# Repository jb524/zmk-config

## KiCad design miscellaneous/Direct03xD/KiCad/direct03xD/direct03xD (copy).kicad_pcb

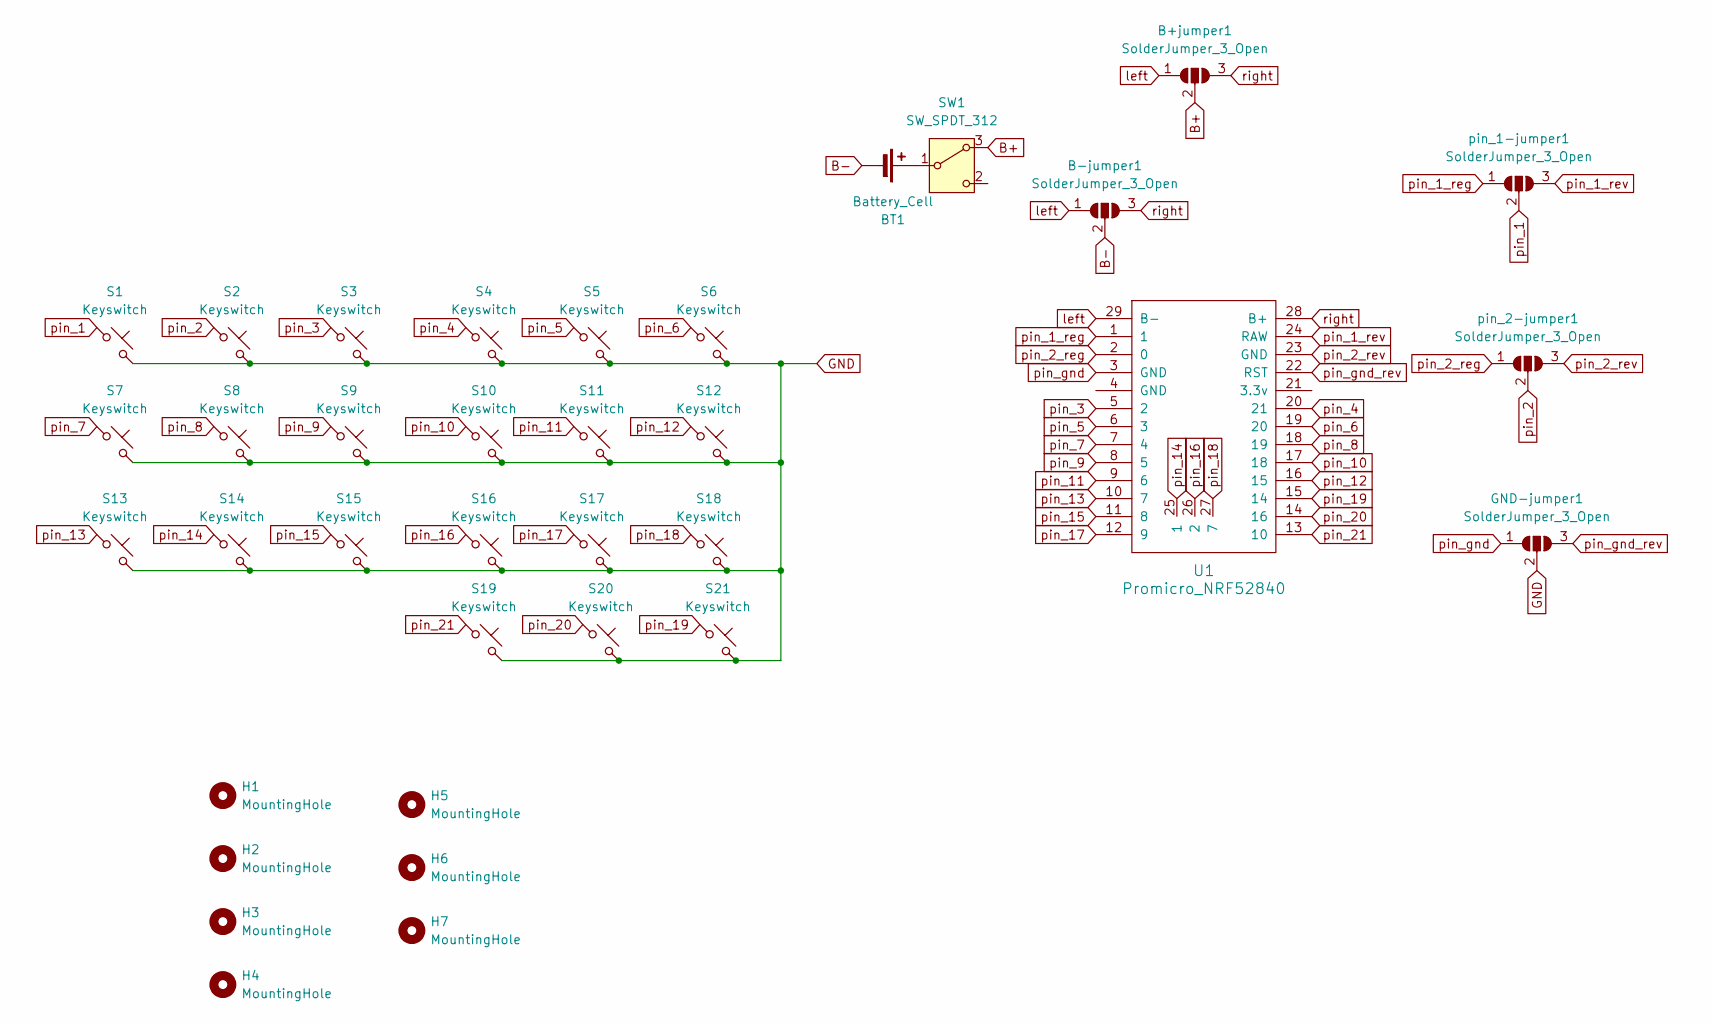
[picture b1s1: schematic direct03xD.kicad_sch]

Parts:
B+jumper1: SolderJumper_3_Open; jumper
B-jumper1: SolderJumper_3_Open; jumper
BT1: Battery_Cell; Battery pins
GND-jumper1: SolderJumper_3_Open; jumper
H1, H2, H3, H4, H5, H6, H7: MountingHole; MountingHole_2.2mm_M2
S1, S2, S3, S4, S5, S6, S7, S8, S9, S10, S11, S12, S13, S14, S15, S16, S17, S18, S19, S20, S21: Keyswitch; MX_1.00u_reversible_solderswap_18.5mm
SW1: SW_SPDT_312; powerswitch_SK12D07VG
U1: Promicro_NRF52840; Promicro_nrf52840_unprinted
pin_1-jumper1, pin_2-jumper1: SolderJumper_3_Open; jumper

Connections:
B+: B+jumper1.2 (C), SW1.3 (A)
B-: B-jumper1.2 (C), BT1.2 (-)
GND: GND-jumper1.2 (C), S1.2, S2.2, S3.2, S4.2, S5.2, S6.2, S7.2, S8.2, S9.2, S10.2, S11.2, S12.2, S13.2, S14.2, S15.2, S16.2, S17.2, S18.2, S19.2, S20.2, S21.2
unnamed: BT1.1 (+), SW1.1 (B)
left: B+jumper1.1 (A), B-jumper1.1 (A), U1.29 (B-)
pin_1: S1.1, pin_1-jumper1.2 (C)
pin_1_reg: U1.1, pin_1-jumper1.1 (A)
pin_1_rev: U1.24 (RAW), pin_1-jumper1.3 (B)
pin_2: S2.1, pin_2-jumper1.2 (C)
pin_2_reg: U1.2 (0), pin_2-jumper1.1 (A)
pin_2_rev: U1.23 (GND), pin_2-jumper1.3 (B)
pin_3: S3.1, U1.5 (2)
pin_4: S4.1, U1.20 (21)
pin_5: S5.1, U1.6 (3)
pin_6: S6.1, U1.19 (20)
pin_7: S7.1, U1.7 (4)
pin_8: S8.1, U1.18 (19)
pin_9: S9.1, U1.8 (5)
pin_10: S10.1, U1.17 (18)
pin_11: S11.1, U1.9 (6)
pin_12: S12.1, U1.16 (15)
pin_13: S13.1, U1.10 (7)
pin_14: S14.1, U1.25 (1)
pin_15: S15.1, U1.11 (8)
pin_16: S16.1, U1.26 (2)
pin_17: S17.1, U1.12 (9)
pin_18: S18.1, U1.27 (7)
pin_19: S21.1, U1.15 (14)
pin_20: S20.1, U1.14 (16)
pin_21: S19.1, U1.13 (10)
pin_gnd: GND-jumper1.1 (A), U1.3 (GND)
pin_gnd_rev: GND-jumper1.3 (B), U1.22 (RST)
right: B+jumper1.3 (B), B-jumper1.3 (B), U1.28 (B+)

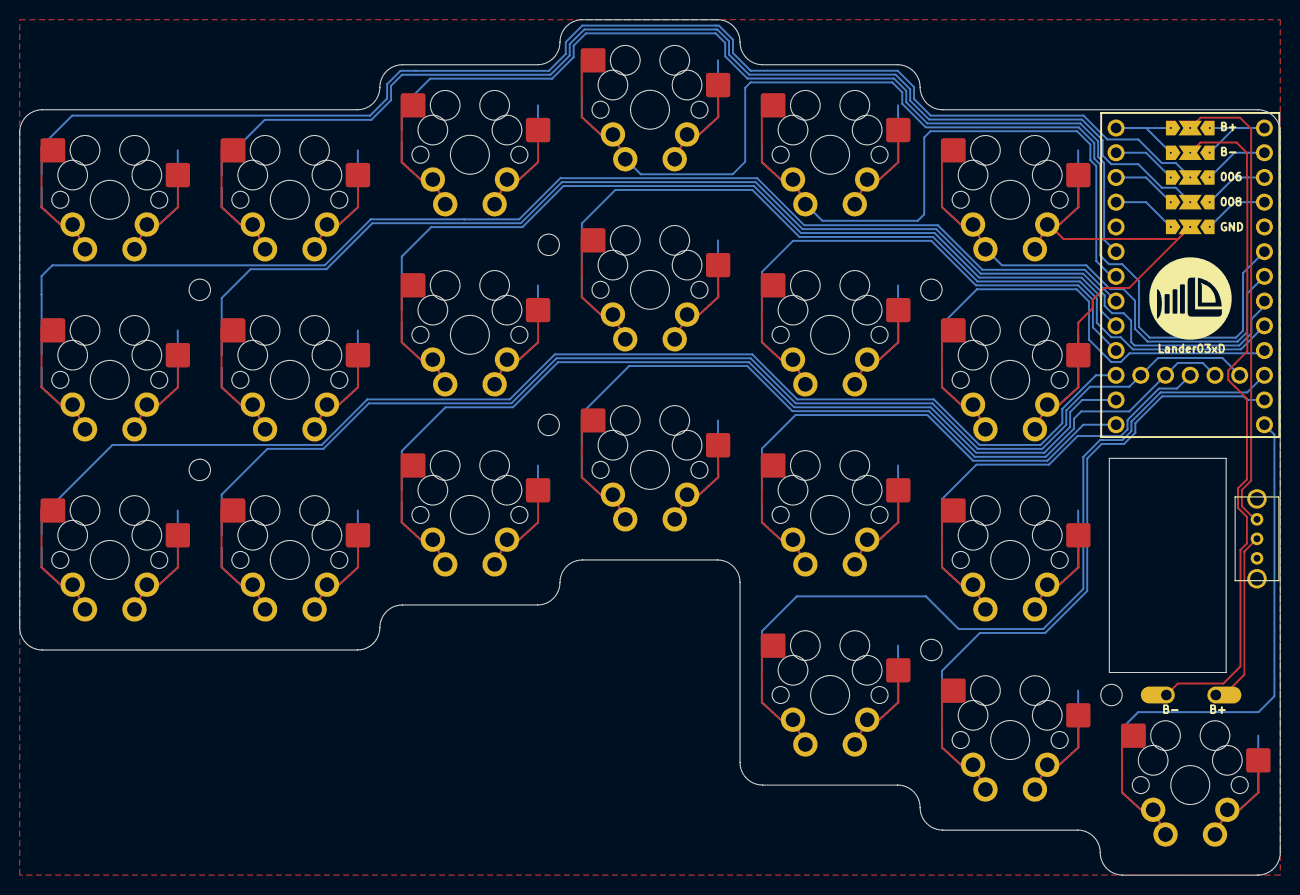
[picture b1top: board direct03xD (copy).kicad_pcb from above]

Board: 2 copper layers, 129.5 x 87.9 mm, 36 parts (0 on the bottom side), 33 nets.

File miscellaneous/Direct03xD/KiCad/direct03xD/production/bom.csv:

Designator,Footprint,Quantity,Value,LCSC Part #
BT1,Battery pins,1,Battery_Cell,
"S1, S10, S11, S12, S13, S14, S15, S16, S17, S18, S19, S2, S20, S21, S3, S4, S5, S6, S7, S8, S9",MX_1.00u_reversible_solderswap_18.5mm,21,Keyswitch,
SW1,powerswitch_SK12D07VG,1,SW_SPDT_312,
U1,Promicro_nrf52840_unprinted,1,Promicro_NRF52840,

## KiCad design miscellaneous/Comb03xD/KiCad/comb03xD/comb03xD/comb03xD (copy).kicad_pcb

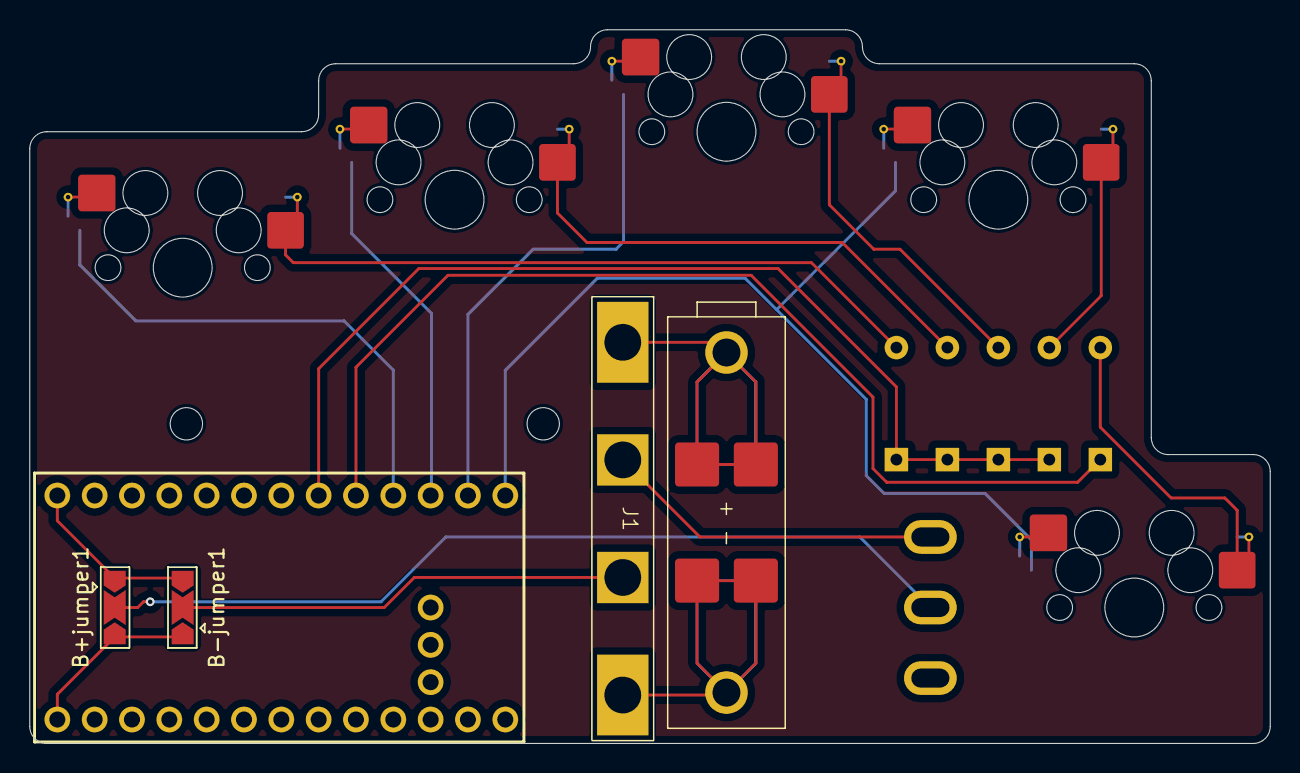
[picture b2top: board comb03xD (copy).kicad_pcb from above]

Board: 2 copper layers, 84.4 x 48.6 mm, 18 parts (0 on the bottom side), 18 nets.

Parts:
B+jumper1: SolderJumper_3_Open; SolderJumper-3_P2.0mm_Open_TrianglePad1.0x1.5mm
B-jumper1: SolderJumper_3_Open; SolderJumper-3_P2.0mm_Open_TrianglePad1.0x1.5mm
BT1: Battery_Cell; SbM-9202_14250_battery_holder
D1, D2, D3, D4, D5: Diode; Diode_DO-35_DO35_unprinted
H1, H2: MountingHole; MountingHole_2.2mm_M2
J1: Conn_01x04_Socket; BMS 1S
S1, S2, S3, S4, S5: Keyswitch; Hotswap_MX_1.00u_reversible_18.5mm
SW1: SW_SPDT_312; SW_Vertical_Slide_5mm
U1: Promicro_NRF52840; Promicro_nrf52840

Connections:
B+: BT1.1 (+), J1.1
B-: BT1.2 (-), J1.4
unnamed: D1.2 (A), S1.2
unnamed: D2.2 (A), S2.2
unnamed: D3.2 (A), S3.2
unnamed: D4.2 (A), S4.2
unnamed: D5.2 (A), S5.2
P+: B+jumper1.2 (C), SW1.1 (B)
P-: B-jumper1.2 (C), J1.3
Ps+: J1.2, SW1.3 (A)
col_1: S1.1, U1.16 (15)
col_2: S2.1, U1.15 (14)
col_3: S3.1, U1.14 (16)
col_4: S4.1, S5.1, U1.13 (10)
left: B+jumper1.3 (B), B-jumper1.1 (A), U1.29 (B-)
right: B+jumper1.1 (A), B-jumper1.3 (B), U1.28 (B+)
row_1: D1.1 (K), D2.1 (K), D3.1 (K), D4.1 (K), U1.18 (19)
row_2: D5.1 (K), U1.17 (18)

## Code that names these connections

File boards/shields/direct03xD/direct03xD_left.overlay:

#include "direct03xD.dtsi" // The shared dtsi file is included in the overlay

// Label of the kscan node in the dtsi
&default_kscan {
	input-gpios =  <&gpio0 6 (GPIO_ACTIVE_LOW | GPIO_PULL_UP)>, //Pin_1
			    <&gpio0 8 (GPIO_ACTIVE_LOW | GPIO_PULL_UP)>,//Pin_2
			    <&gpio0 17 (GPIO_ACTIVE_LOW | GPIO_PULL_UP)>,//Pin_3
			    <&gpio0 31 (GPIO_ACTIVE_LOW | GPIO_PULL_UP)>,//Pin_4
			    <&gpio0 20 (GPIO_ACTIVE_LOW | GPIO_PULL_UP)>,//Pin_5
			    <&gpio0 29 (GPIO_ACTIVE_LOW | GPIO_PULL_UP)>,//Pin_6
			    <&gpio0 22 (GPIO_ACTIVE_LOW | GPIO_PULL_UP)>,//Pin_7
			    <&gpio0 2 (GPIO_ACTIVE_LOW | GPIO_PULL_UP)>,//Pin_8
			    <&gpio0 24 (GPIO_ACTIVE_LOW | GPIO_PULL_UP)>,//Pin_9
			    <&gpio1 15 (GPIO_ACTIVE_LOW | GPIO_PULL_UP)>,//Pin_10
			    <&gpio1 0 (GPIO_ACTIVE_LOW | GPIO_PULL_UP)>,//Pin_11
			    <&gpio1 13 (GPIO_ACTIVE_LOW | GPIO_PULL_UP)>,//Pin_12
			    <&gpio0 11  (GPIO_ACTIVE_LOW | GPIO_PULL_UP)>,//Pin_13
			    <&gpio1 1 (GPIO_ACTIVE_LOW | GPIO_PULL_UP)>,//Pin_14
			    <&gpio1 4 (GPIO_ACTIVE_LOW | GPIO_PULL_UP)>,//Pin_15
			    <&gpio1 2 (GPIO_ACTIVE_LOW | GPIO_PULL_UP)>,//Pin_16
			    <&gpio1 6  (GPIO_ACTIVE_LOW | GPIO_PULL_UP)>,//Pin_17
			    <&gpio1 7 (GPIO_ACTIVE_LOW | GPIO_PULL_UP)>,//Pin_18
			    <&gpio1 11 (GPIO_ACTIVE_LOW | GPIO_PULL_UP)>,//Pin_19
			    <&gpio0 10  (GPIO_ACTIVE_LOW | GPIO_PULL_UP)>,//Pin_20
			    <&gpio0 9  (GPIO_ACTIVE_LOW | GPIO_PULL_UP)>//Pin_21
			    ;
};

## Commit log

2026-01-29 correct pins on crab03xD
2026-01-29 correct gpio pins again
2026-01-29 build the correct firmware you dummy
2026-01-29 reverting to correct keycodes
2026-02-01 build steno
2026-02-01 correct steno pinout
2026-02-12 morse code custom behhavior
2026-02-12 moved the dts to the correct config location
2026-02-12 moved bindings once more
2026-02-12 fixing more mistakes , maybe I just read the documentation
2026-02-12 oh well
2026-02-12 morse code
2026-02-12 did I do something?
2026-02-12 vibe coding isn't my vibe
2026-02-15 build crab
2026-02-26 created a tester config for mcu beards
2026-02-26 fixed the gpio issue
2026-02-26 added firmware
2026-02-26 added morse and ceasar to my keymap
2026-02-26 added include
2026-03-02 added debugging
2026-03-02 added a second snippet?
2026-03-02 one more time!
2026-03-02 changed tap-hold
2026-03-03 added balanced mod tap
2026-03-03 added config_zmk_board_compat
2026-03-03 added it everywhere losing hope
2026-03-03 REEEEEEE
2026-03-03 test
2026-03-03 one more try
2026-03-03 lets see
2026-03-07 common layout
2026-03-07 rename filetype
2026-03-07 added accents for local search while building
2026-03-07 moved more to common layout
2026-03-07 build fishkeeb
2026-03-07 changed module path
2026-03-07 noise key attempt
2026-03-07 add usb logging
2026-03-07 build for cheap03xD
2026-03-12 updated steno pins
2026-03-12 build for steno
2026-03-12 bild for steno
2026-03-14 sten02xD
2026-03-14 sten03xD
2026-03-14 build again I guess
2026-03-14 removed nkro
2026-03-14 removed zmk studio support
2026-03-14 stengraphy finally working?
2026-03-14 testing nkro settings
2026-03-14 changed nkro config
2026-03-14 attempt for new config
2026-03-14 setting it in config folder
2026-03-14 added remove
2026-03-15 build for splitfish
2026-03-15 spelling mistake
2026-03-21 add logging to right side
2026-03-21 logging to left side
2026-03-21 addede logging agaiyn?
2026-03-21 cheap03xD build for split fish attempt to fix my mistakes I guess
2026-03-22 splitFish code
2026-03-22 rename file
2026-03-29 added gerber files for direct03xD
2026-03-31 chord03xD
2026-03-31 changed name
2026-03-31 fixed LS
2026-03-31 corrected unique combo names
2026-03-31 split layer specific combos
2026-03-31 removed duplicate
2026-03-31 fixed layer issue
2026-03-31 layerS
2026-03-31 fixed config
2026-04-01 deleted backup files to clean git a bit and added chord kicad
2026-04-01 Test if gitignore works
2026-04-01 left chord03xD
2026-04-04 zmk unlock added
2026-04-04 added zmk support
2026-04-04 removed duplicate curlybrackets
2026-04-04 import added
2026-04-04 added correct label
2026-04-04 added correct laber again
2026-04-04 one phandle
2026-04-04 i'm the monkey
2026-04-04 tapholds need 2 bindings
2026-04-04 added initial push for direct03xD
2026-04-04 fixed layout and keymap
2026-04-04 building for the right keyboard
2026-04-04 overlay left missed a comma
2026-04-04 fixed keymap
2026-04-04 commas
2026-04-04 adding loggin to right half
2026-04-04 fix chord like described
2026-04-04 corrected labels
2026-04-04 correct zmk unlock key
2026-04-30 correcting gpio pins
2026-04-30 corrected shit
2026-04-30 build for correct board
2026-04-30 comma by moving pins
2026-04-30 rearranging pins again
2026-04-30 commas man
2026-04-30 losing my fucking mind
2026-04-30 this should be the one
2026-04-30 correct pins left
2026-05-01 fixing the layout a bit
2026-05-01 did I change anything?
2026-05-01 pushing steno toggle changes
2026-05-01 rearrange steno
2026-05-03 added shift in second layer
2026-05-14 building the experimental keymap layout
2026-05-14 keycode corrections
2026-05-14 fixed some keymap issues
2026-05-14 give me errors
2026-05-14 i'm a monkey issues was lshift instead of shirt
2026-05-14 experimental v2
2026-05-14 expv3
2026-05-15 created layout v6
2026-05-15 correction in the v6
2026-05-18 Enable chord03xD build
2026-05-19 Customize chord03xD keymap: combos, SYS layer, tuned hold-taps
2026-05-19 Fix devicetree error: bake tap-dance params, drop macro wrappers
2026-05-19 Fix hold-tap bindings: use forwarded params not baked
2026-05-19 Fix hold-tap: symmetric 1+1 bindings with macro wrappers for tap-dances
2026-05-20 Fix hold-mod sticky timeout and combo_1_012 double-tap timing
2026-05-20 Remove 4 unused legacy behaviors from lander03xD template
